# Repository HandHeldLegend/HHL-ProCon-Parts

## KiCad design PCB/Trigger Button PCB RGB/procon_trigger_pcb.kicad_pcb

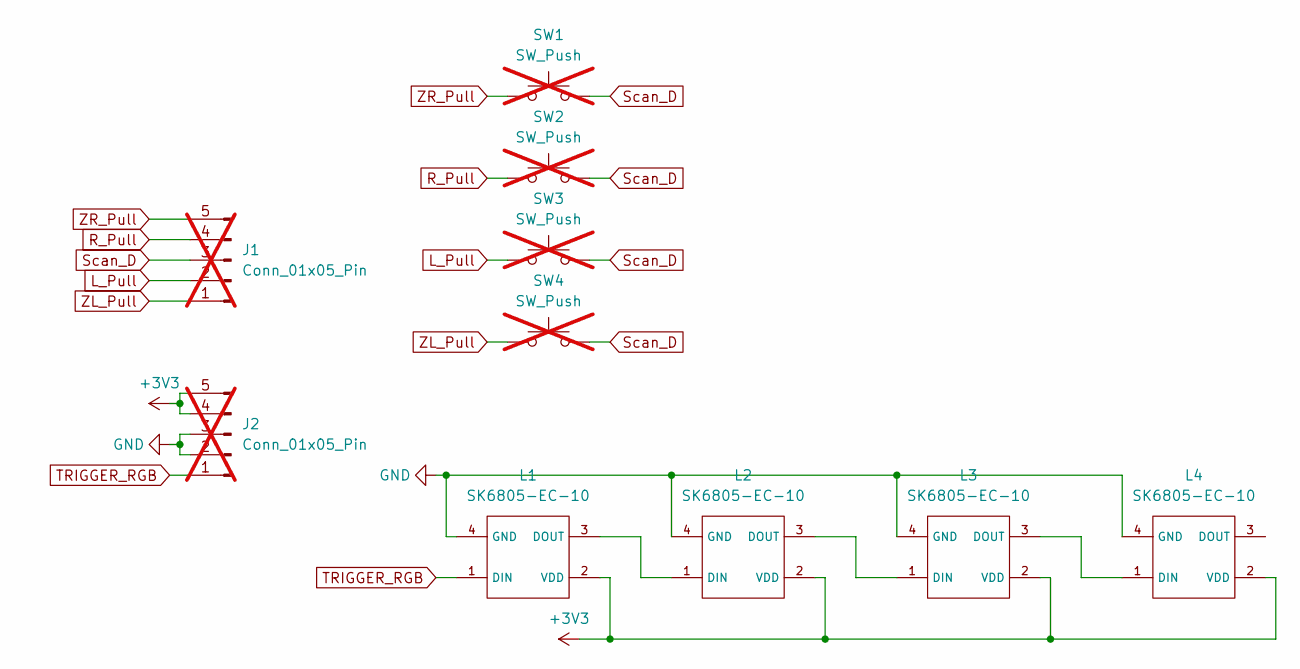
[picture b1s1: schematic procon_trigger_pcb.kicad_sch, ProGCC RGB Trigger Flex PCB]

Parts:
J1, J2: Conn_01x05_Pin; molex_5034800540_ribbon; not fitted
L1, L2, L3, L4: SK6805-EC-10; MPN SK6805-EC-10
SW1, SW2, SW3, SW4: SW_Push; starprint; not fitted

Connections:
+3V3: J2.4, J2.5, L1.2 (VDD), L2.2 (VDD), L3.2 (VDD), L4.2 (VDD)
GND: J2.2, J2.3, L1.4 (GND), L2.4 (GND), L3.4 (GND), L4.4 (GND)
L_Pull: J1.2, SW3.1
unnamed: L1.3 (DOUT), L2.1 (DIN)
unnamed: L2.3 (DOUT), L3.1 (DIN)
unnamed: L3.3 (DOUT), L4.1 (DIN)
R_Pull: J1.4, SW2.1
Scan_D: J1.3, SW1.2, SW2.2, SW3.2, SW4.2
TRIGGER_RGB: J2.1, L1.1 (DIN)
ZL_Pull: J1.1, SW4.1
ZR_Pull: J1.5, SW1.1

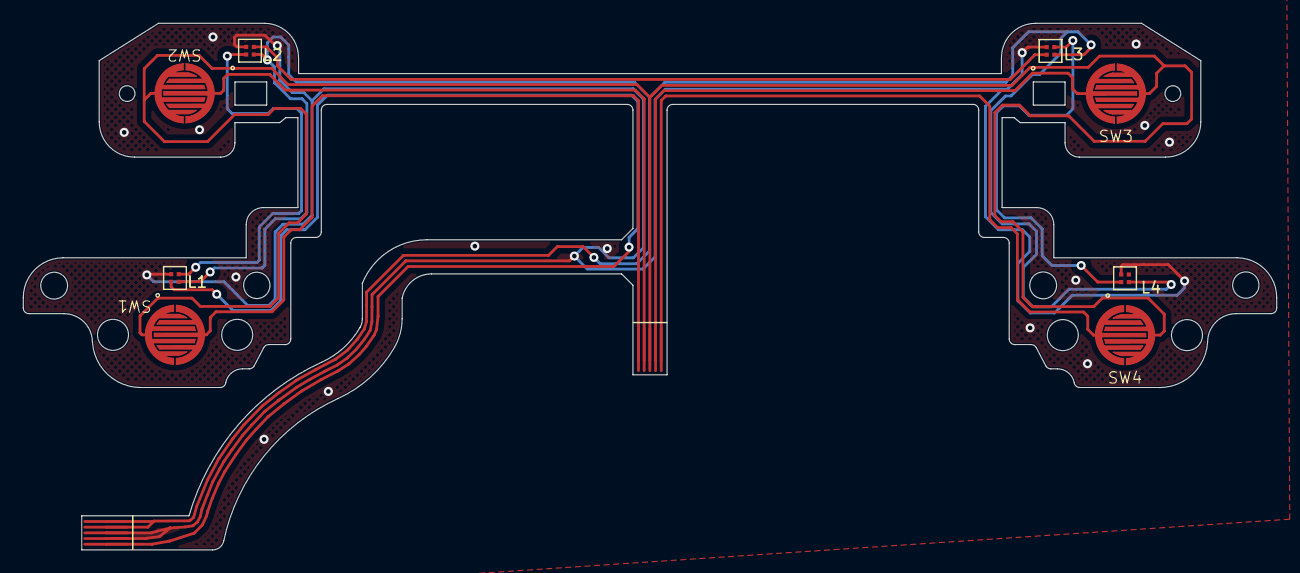
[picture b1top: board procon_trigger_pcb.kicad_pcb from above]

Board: 2 copper layers, 110.3 x 46.3 mm, 10 parts (0 on the bottom side), 11 nets.

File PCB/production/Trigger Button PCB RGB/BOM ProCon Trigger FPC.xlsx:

NO | Designator | Quantity | Part Number（MPN) | Description | Value | Package | LCSC | Comment or Link | DNP
1.0 | J1,J2 | 2.0 | - | - | Conn_01x05_Pin | - | - | - | DNP
2.0 | L1,L2,L3,L4 | 4.0 | SK6805-EC-10 | RGB LED | SK6805-EC-10 | SK6805-EC-10
3.0 | SW1,SW2,SW3,SW4 | 4.0 |  |  | SW_Push |  |  |  | DNP

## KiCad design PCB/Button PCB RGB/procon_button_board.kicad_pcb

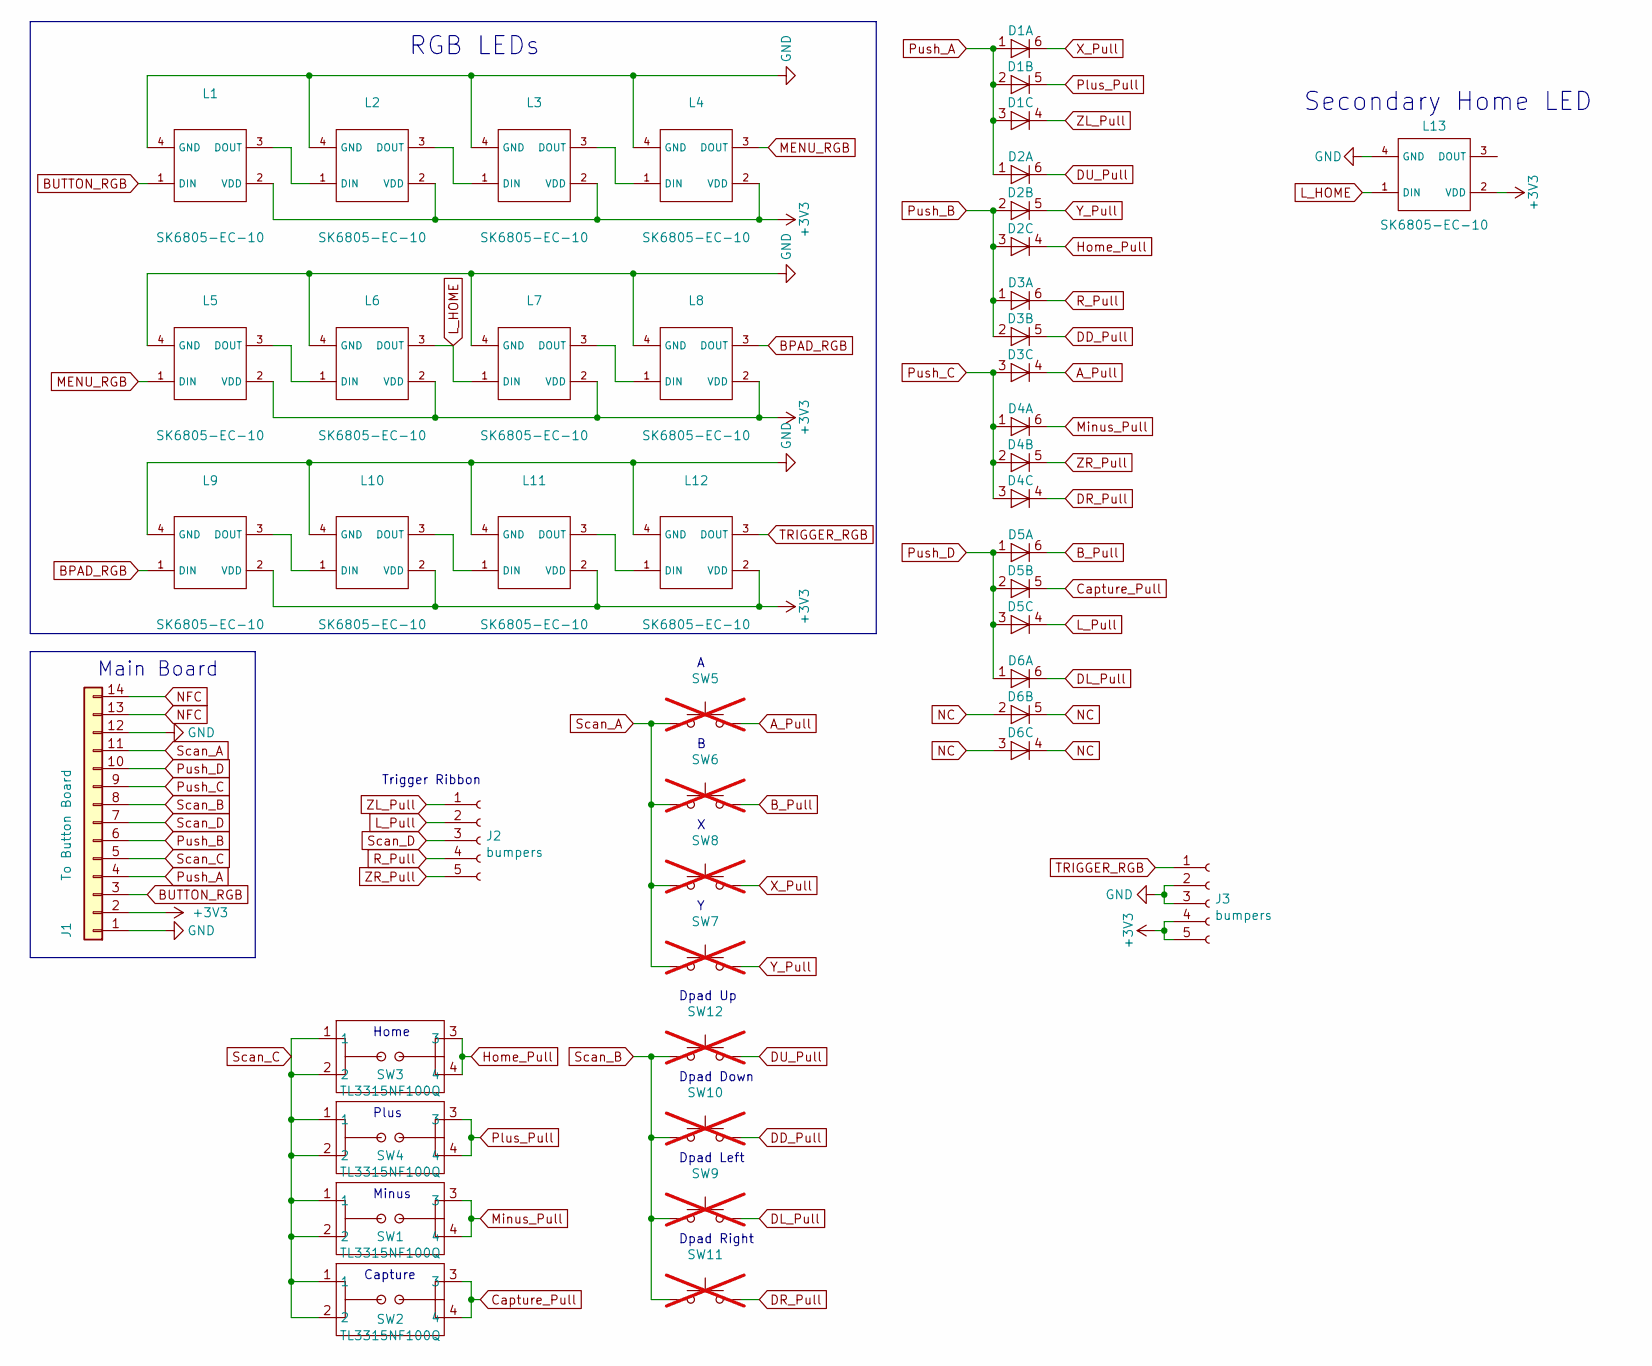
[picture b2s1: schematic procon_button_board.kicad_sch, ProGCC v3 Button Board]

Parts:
D1, D2, D3, D4, D5, D6: BAS16VY,115; SOT-363_SC-70-6; MPN BAS16VY,115
J1: To Button Board; molex_5051101492_14P; MPN molex_5051101492_14P
J2, J3: bumpers; molex_5034800540; MPN molex_5034800540
L1, L2, L3, L4, L5, L6, L7, L8, L9, L10, L11, L12, L13: SK6805-EC-10; MPN SK6805-EC-10
SW1, SW2, SW3, SW4: TL3315NF100Q; PTS540JM035SMTRLFS; MPN PTS540JM035SMTRLFS
SW5, SW6, SW7, SW8: BPAD; ring_pad; not fitted
SW9, SW10, SW11, SW12: DPAD; ring_dpad; not fitted

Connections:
+3V3: J1.2, J3.4, J3.5, L1.2 (VDD), L2.2 (VDD), L3.2 (VDD), L4.2 (VDD), L5.2 (VDD), L6.2 (VDD), L7.2 (VDD), L8.2 (VDD), L9.2 (VDD), L10.2 (VDD), L11.2 (VDD), L12.2 (VDD), L13.2 (VDD)
A_Pull: D3.4 (K), SW5.2
BPAD_RGB: L8.3 (DOUT), L9.1 (DIN)
BUTTON_RGB: J1.3, L1.1 (DIN)
B_Pull: D5.6 (K), SW6.2
Capture_Pull: D5.5 (K), SW2.3, SW2.4
DD_Pull: D3.5 (K), SW10.2
DL_Pull: D6.6 (K), SW9.2
DR_Pull: D4.4 (K), SW11.2
DU_Pull: D2.6 (K), SW12.2
GND: J1.1, J1.12, J3.2, J3.3, L1.4 (GND), L2.4 (GND), L3.4 (GND), L4.4 (GND), L5.4 (GND), L6.4 (GND), L7.4 (GND), L8.4 (GND), L9.4 (GND), L10.4 (GND), L11.4 (GND), L12.4 (GND), L13.4 (GND)
Home_Pull: D2.4 (K), SW3.3, SW3.4
L_HOME: L6.3 (DOUT), L7.1 (DIN), L13.1 (DIN)
L_Pull: D5.4 (K), J2.2
MENU_RGB: L4.3 (DOUT), L5.1 (DIN)
Minus_Pull: D4.6 (K), SW1.3, SW1.4
NC: D6.2 (A), D6.3 (A), D6.4 (K), D6.5 (K)
NFC: J1.13, J1.14
unnamed: L1.3 (DOUT), L2.1 (DIN)
unnamed: L2.3 (DOUT), L3.1 (DIN)
unnamed: L3.3 (DOUT), L4.1 (DIN)
unnamed: L5.3 (DOUT), L6.1 (DIN)
unnamed: L7.3 (DOUT), L8.1 (DIN)
unnamed: L9.3 (DOUT), L10.1 (DIN)
unnamed: L10.3 (DOUT), L11.1 (DIN)
unnamed: L11.3 (DOUT), L12.1 (DIN)
Plus_Pull: D1.5 (K), SW4.3, SW4.4
Push_A: D1.1 (A), D1.2 (A), D1.3 (A), D2.1 (A), J1.4
Push_B: D2.2 (A), D2.3 (A), D3.1 (A), D3.2 (A), J1.6
Push_C: D3.3 (A), D4.1 (A), D4.2 (A), D4.3 (A), J1.9
Push_D: D5.1 (A), D5.2 (A), D5.3 (A), D6.1 (A), J1.10
R_Pull: D3.6 (K), J2.4
Scan_A: J1.11, SW5.1, SW6.1, SW7.1, SW8.1
Scan_B: J1.8, SW9.1, SW10.1, SW11.1, SW12.1
Scan_C: J1.5, SW1.1, SW1.2, SW2.1, SW2.2, SW3.1, SW3.2, SW4.1, SW4.2
Scan_D: J1.7, J2.3
TRIGGER_RGB: J3.1, L12.3 (DOUT)
X_Pull: D1.6 (K), SW8.2
Y_Pull: D2.5 (K), SW7.2
ZL_Pull: D1.4 (K), J2.1
ZR_Pull: D4.5 (K), J2.5

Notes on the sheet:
Plus
Capture
Dpad Right
Main Board
Dpad Up
Dpad Down
Trigger Ribbon
Dpad Left
Secondary Home LED
Home
Minus
RGB LEDs

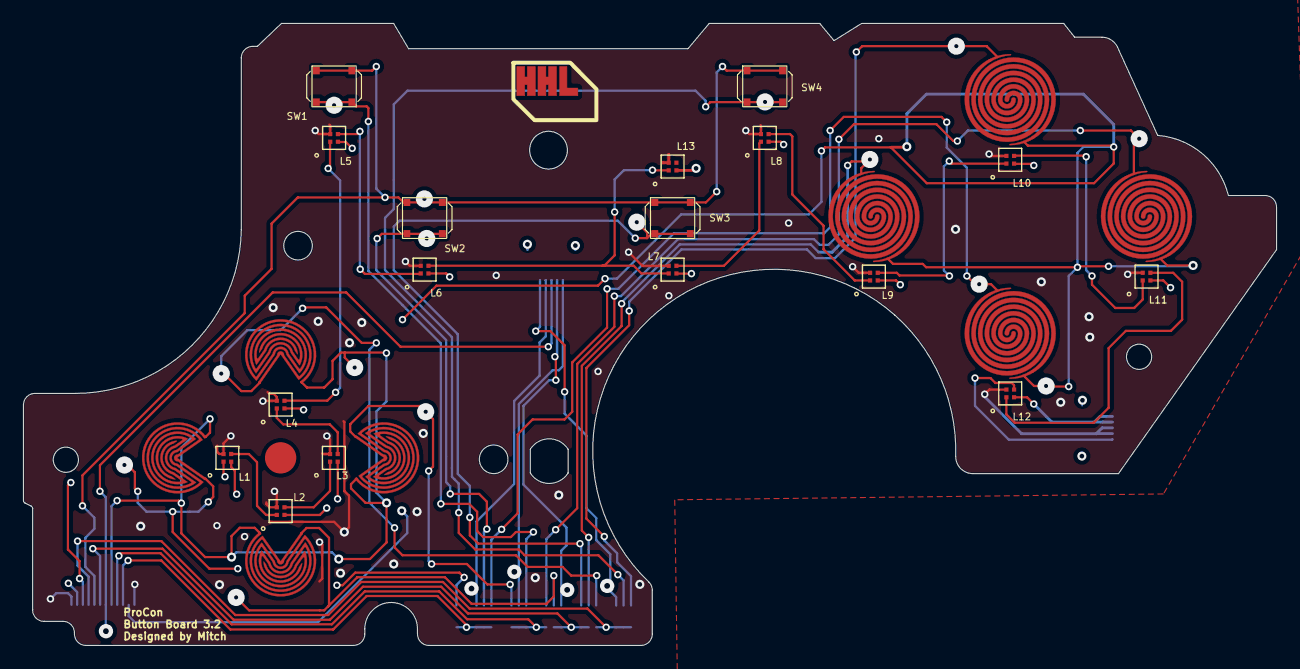
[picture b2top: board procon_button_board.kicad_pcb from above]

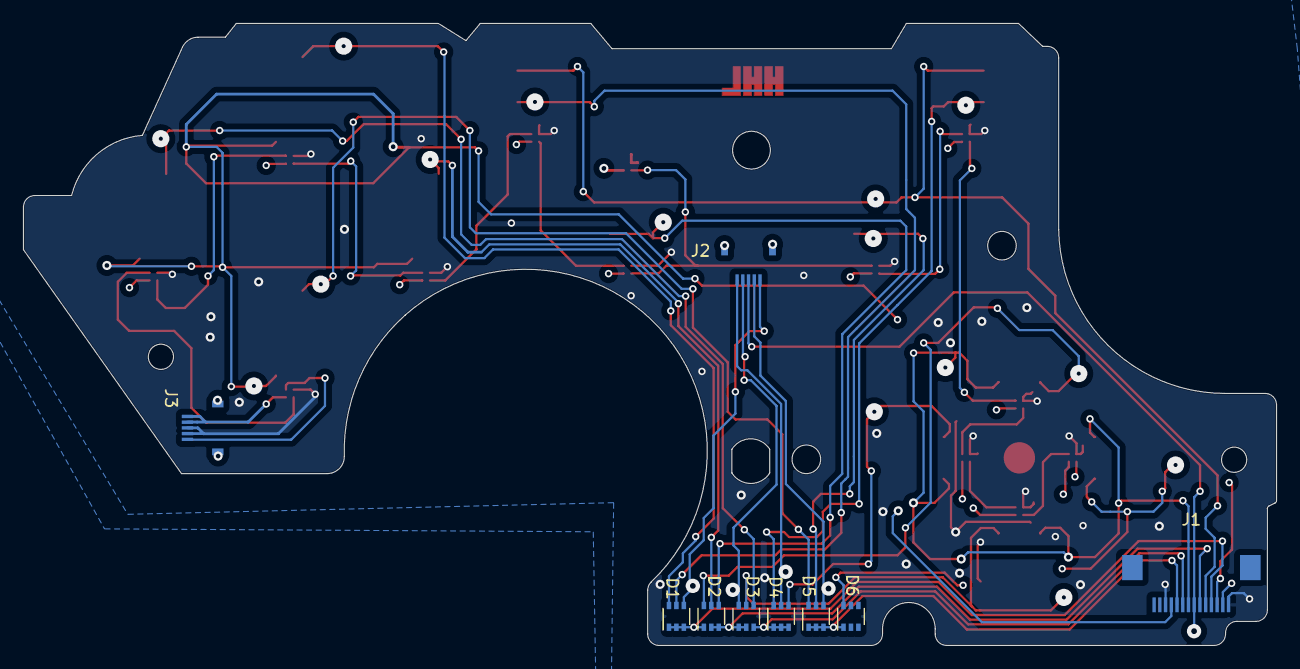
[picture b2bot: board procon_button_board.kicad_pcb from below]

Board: 4 copper layers, 109.4 x 54.3 mm, 34 parts (9 on the bottom side), 41 nets.

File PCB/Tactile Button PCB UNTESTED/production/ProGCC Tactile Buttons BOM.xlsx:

# | Reference | Qty | Value | Footprint | DNP | MPN
1.0 | D1, D2, D3, D4, D5, D6 | 6.0 | BAS16VY,115 | Package_TO_SOT_SMD:SOT-363_SC-70-6
2.0 | J1 | 1.0 | To Button Board | hhl:molex_5051101492_14P |  | molex_5051101492_14P
3.0 | J2 | 1.0 | bumpers | hhl:molex_5034800540 |  | molex_5034800540
4.0 | L1, L2, L3, L4, L5, L6, L7, L8, L9, L10, L11, L12 | 12.0 | SK6805-EC-15 | hhl:SK6805-EC-15
5.0 | SW1, SW2, SW3, SW4 | 4.0 | TL3315NF100Q | hhl:PTS540JM035SMTRLFS |  | PTS540JM035SMTRLFS
6.0 | SW5, SW6, SW7, SW8, SW9, SW10, SW11, SW12 | 8.0 | BPAD, DPAD | hhl:EVPBT2C4A000 |  | EVPBT2A4A000

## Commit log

2023-09-27 Add PCB Section
2023-09-27 Update lib to submodule
2023-09-28 Add tactile button pcb
2023-09-28 Update with battery PCB
2023-09-28 remove lock file
2024-02-23 Update with split dpad file test
2024-03-06 Updates to PCBs all around
2024-09-01 Update component BOM and production files.
2024-10-30 Update production files
2024-10-30 Add new BOMs
2024-11-30 Update trigger flex pcb
2024-12-03 Expand solder mask on FPC led pads
